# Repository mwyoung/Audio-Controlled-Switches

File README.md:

# Audio Controlled Switches

Oregon State University ECE Senior Project

By Jinshuai Gan (electrical work), Joseph Swelland (microphone, audio), and Miles Young (microcontroller, rx/tx, PCB).

Wifi code from Davide Gironi (GPLv3).

## Setup

The Hub folder contains code for the main controller with a microphone. The output folders
each control a specific output or PWM motor.

The PCB for each was identical, with the hub containing different parts than the output
devices.

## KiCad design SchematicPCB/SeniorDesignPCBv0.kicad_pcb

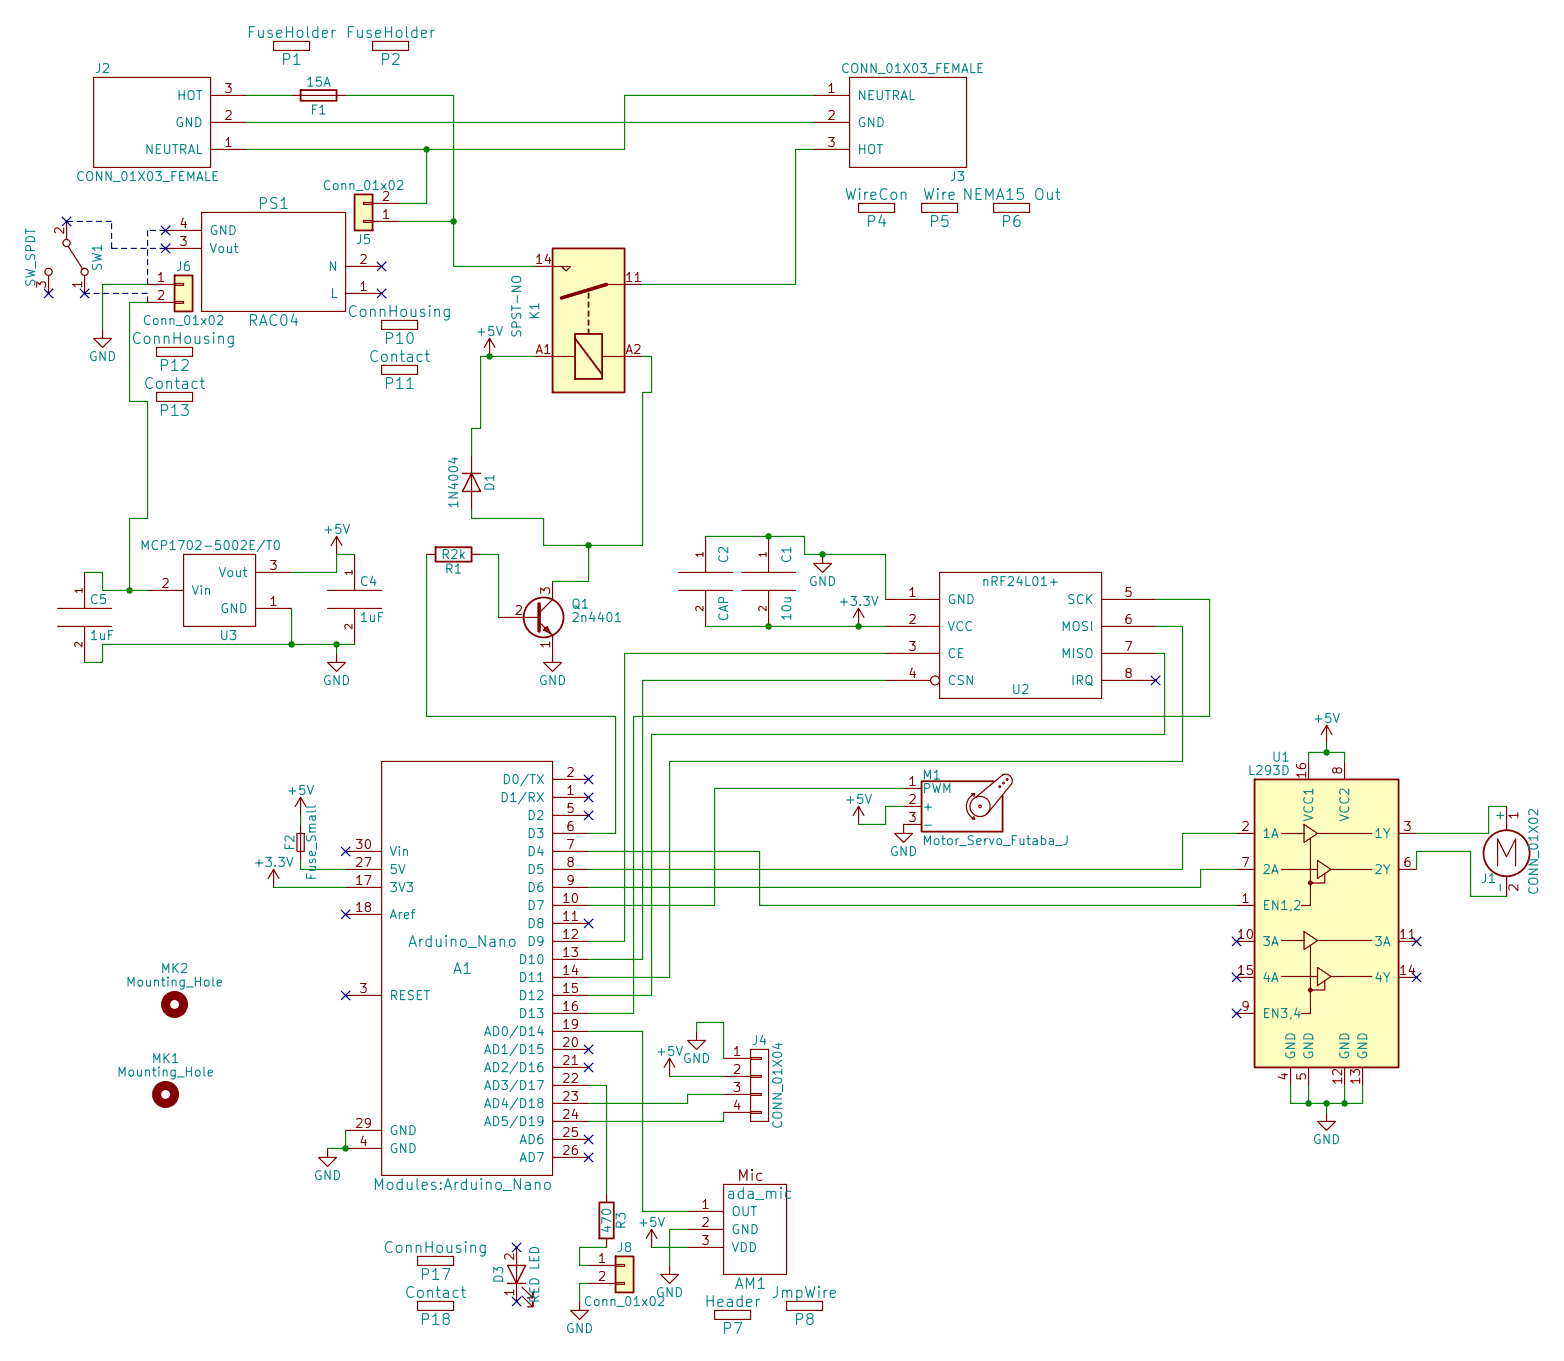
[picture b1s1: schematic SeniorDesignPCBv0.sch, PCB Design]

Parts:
A1: Arduino_Nano; Manufacturer Part # EL-CB-005
AM1: ada_mic; ADA_mic; Manufacturer Part # Adafruit MAX4466 Electret Mic Amplifier
C1: 10u; CP_Radial_D5.0mm_P2.00mm; Manufacturer Part # 860020472003
C2: CAP; C_Rect_L7.0mm_W2.5mm_P5.00mm; Manufacturer Part # K101K10X7RH5UH5
C4, C5: 1uF; CP_Radial_Tantal_D4.5mm_P2.50mm; Manufacturer Part # FG18X5R1H105KRT06
D1: 1N4004; D_A-405_P10.16mm_Horizontal; Manufacturer Part # 1N4004-TP
D3: RED LED; PlaceHolder; Manufacturer Part # C503B-RAN-CZ0C0AA1
F1: 15A; FuseHolder; Manufacturer Part # 3AG 15-R
F2: Fuse_Small; C_Disc_D8.0mm_W2.5mm_P5.00mm; Manufacturer Part # RXEF050
J1: CONN_01X02; Pin_Header_Straight_1x02_Pitch2.54mm; Manufacturer Part # SER0043
J2: CONN_01X03_FEMALE; 703W-1h; Manufacturer Part # 703W-00/53
J3: CONN_01X03_FEMALE; JST_VH_B3P-VH_3x3.96mm_Vertical; Manufacturer Part # B3P-VH(LF)(SN)
J4: CONN_01X04; Pin_Header_Straight_1x04_Pitch2.54mm; Manufacturer Part # M20-9990445
J5, J6, J8: Conn_01x02; JST_EH_B02B-EH-A_02x2.50mm_Straight; Manufacturer Part # B2B-EH-A(LF)(SN)
K1: SPST-NO; Relay_SPST_Schrack-RT1-16A-FormA_RM5mm; Manufacturer Part # RZ03-1A4-D005
M1: Motor_Servo_Futaba_J; Pin_Header_Straight_1x03_Pitch2.54mm; Manufacturer Part # 169
MK1, MK2: Mounting_Hole; MountingHole_3.5mm
P1, P2: FuseHolder; PlaceHolder; Manufacturer Part # FC-102-22
P4: WireCon; PlaceHolder; Manufacturer Part # VHR-3N
P5: Wire; PlaceHolder; Manufacturer Part # ASVHSVH16K152
P6: NEMA15 Out; PlaceHolder; Manufacturer Part # 738W-X2/03
P7: Header; PlaceHolder; Manufacturer Part # 61300311121
P8: JmpWire; PlaceHolder; Manufacturer Part # 1954
P10, P12, P17: ConnHousing; PlaceHolder; Manufacturer Part # EHR-2
P11, P13, P18: Contact; PlaceHolder; Manufacturer Part # SEH-001T-P0.6
PS1: RAC04; PlaceHolder; Manufacturer Part # RAC04-09SC/W
Q1: 2n4401; TO-92_Inline_Wide; Manufacturer Part # 2N4401BU
R1: R2k; R_Axial_DIN0204_L3.6mm_D1.6mm_P7.62mm_Horizontal; Manufacturer Part # CF14JT2K20
R3: 470; R_Axial_DIN0207_L6.3mm_D2.5mm_P10.16mm_Horizontal; Manufacturer Part # CF14JT470R
SW1: SW_SPDT; PlaceHolder; Manufacturer Part # 100SP1T2B4M6QE
U1: L293D; DIP-16_W7.62mm; Manufacturer Part # L239D
U2: nRF24L01+; NRF24L01; Manufacturer Part # BC22523
U3: MCP1702-5002E/T0; TO-92_Inline_Wide; Manufacturer Part # MCP1702-5002E/TO

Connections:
+3V3: A1.17 (3V3), C1.2, C2.2, U2.2 (VCC)
+5V: AM1.3 (VDD), C4.1, D1.1 (K), F2.1, J4.2, K1.A1, M1.2 (+), U1.8 (VCC2), U1.16 (VCC1), U3.3 (Vout)
GND: A1.4 (GND), A1.29 (GND), AM1.2 (GND), C1.1, C2.1, C4.2, C5.2, J4.1, J6.1, J8.2, M1.3 (-), Q1.1 (E), U1.4 (GND), U1.5 (GND), U1.12 (GND), U1.13 (GND), U2.1 (GND), U3.1 (GND)
unnamed: A1.6 (D3), R1.2
unnamed: A1.7 (D4), U1.1 (EN1,2)
unnamed: A1.8 (D5), U1.2 (1A)
unnamed: A1.9 (D6), U1.7 (2A)
unnamed: A1.10 (D7), M1.1 (PWM)
unnamed: A1.12 (D9), U2.3 (CE)
unnamed: A1.13 (D10), U2.4 (CSN)
unnamed: A1.14 (D11), U2.6 (MOSI)
unnamed: A1.15 (D12), U2.7 (MISO)
unnamed: A1.16 (D13), U2.5 (SCK)
unnamed: A1.19 (AD0/D14), AM1.1 (OUT)
unnamed: A1.22 (AD3/D17), R3.1
unnamed: A1.23 (AD4/D18), J4.3
unnamed: A1.24 (AD5/D19), J4.4
unnamed: A1.27 (5V), F2.2
unnamed: C5.1, J6.2, U3.2 (Vin)
unnamed: D1.2 (A), K1.A2, Q1.3 (C)
unnamed: F1.1, J5.1, K1.14
unnamed: F1.2, J2.3 (HOT)
unnamed: J1.1 (+), U1.3 (1Y)
unnamed: J1.2 (-), U1.6 (2Y)
unnamed: J2.1 (NEUTRAL), J3.1 (NEUTRAL), J5.2
unnamed: J2.2 (GND), J3.2 (GND)
unnamed: J3.3 (HOT), K1.11
unnamed: J8.1, R3.2
unnamed: Q1.2 (B), R1.1

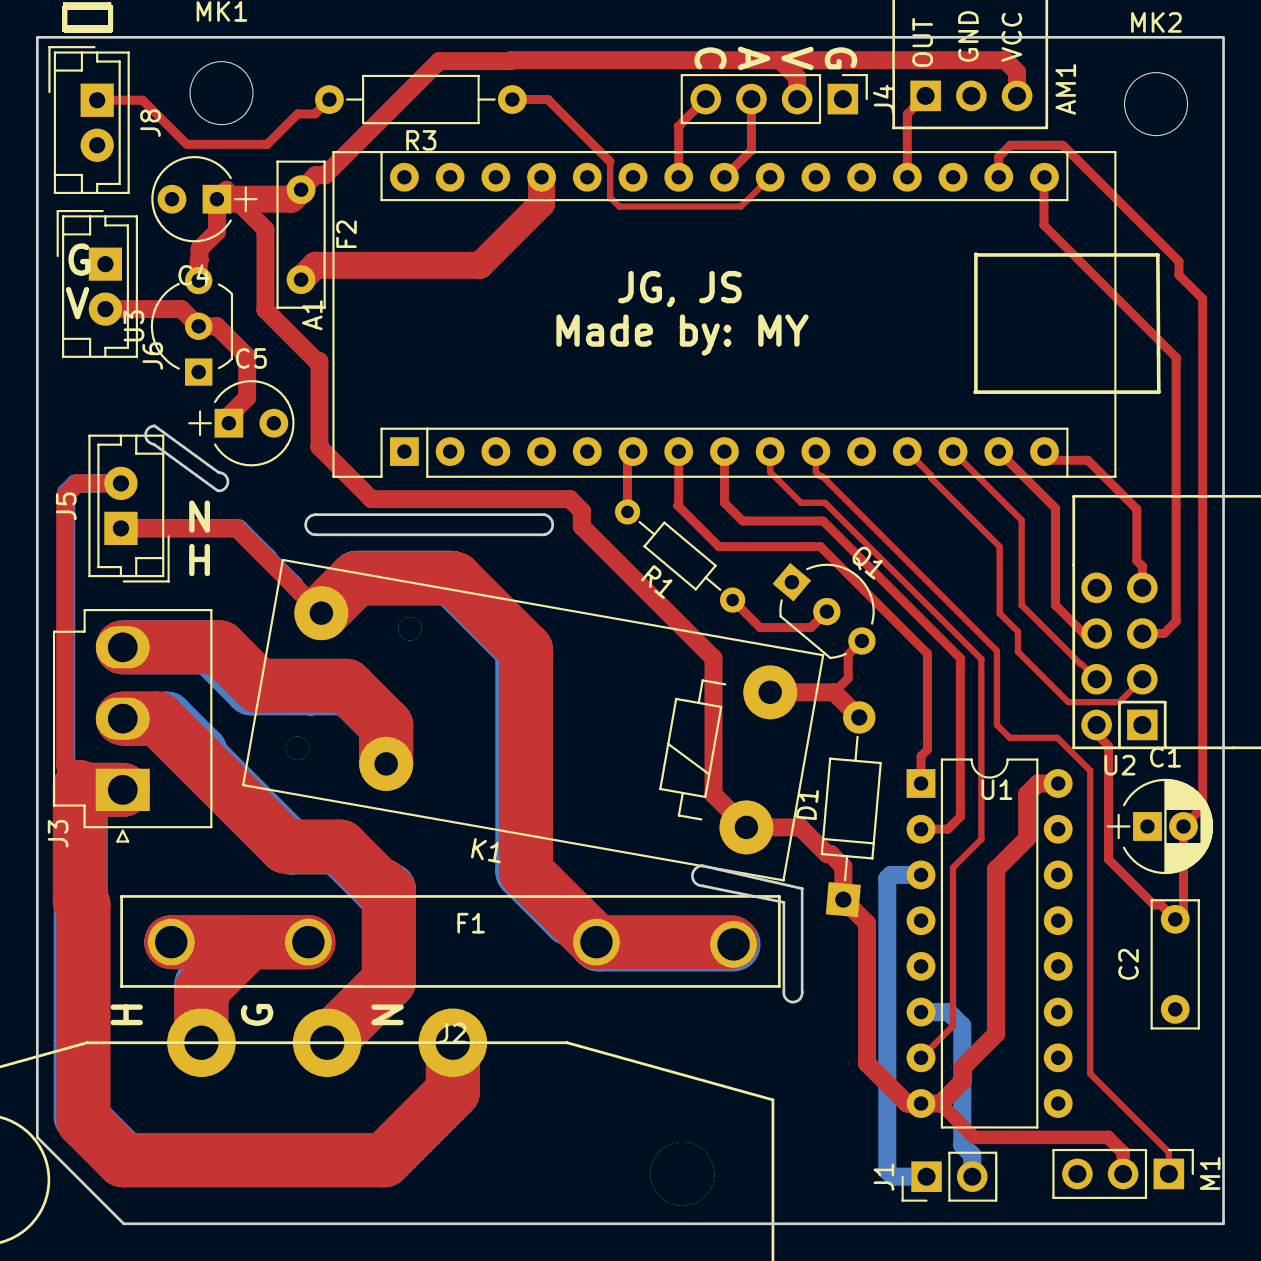
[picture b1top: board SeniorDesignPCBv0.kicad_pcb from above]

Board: 2 copper layers, 65.9 x 65.9 mm, 42 parts (0 on the bottom side), 29 nets.

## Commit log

2019-10-15 Added pdf of schematic
2019-10-15 More information
